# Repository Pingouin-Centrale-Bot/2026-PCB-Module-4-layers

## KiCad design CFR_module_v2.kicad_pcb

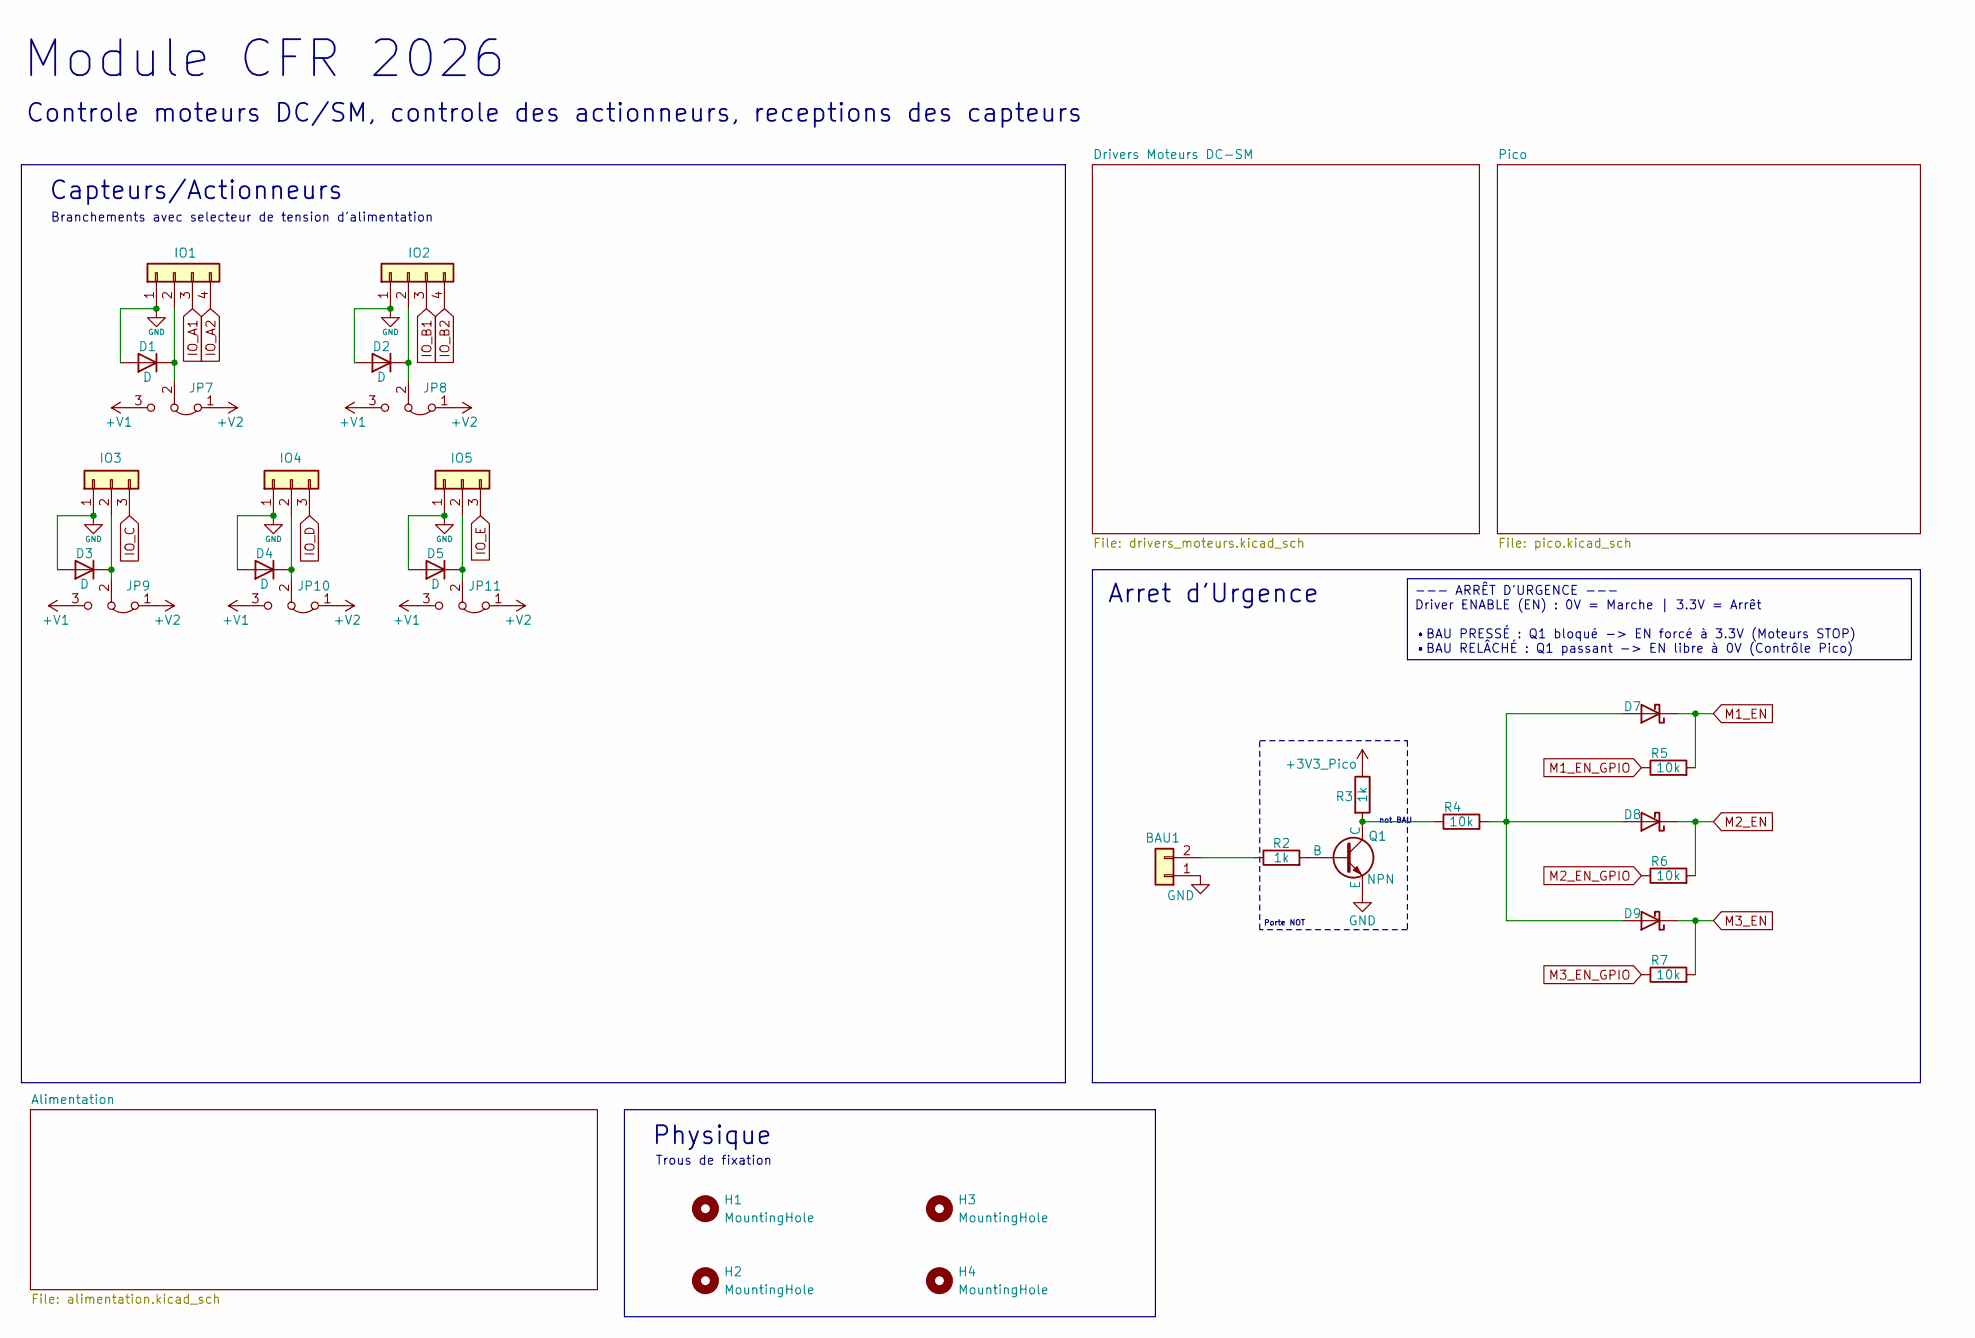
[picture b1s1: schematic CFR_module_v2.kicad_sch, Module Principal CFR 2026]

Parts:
BAU1: Conn_01x02; JST_XH_S2B-XH-A_1x02_P2.50mm_Horizontal
D1, D2, D3, D4, D5: D; D_SMA_Handsoldering
D7, D8, D9: D_Schottky; D_SOD-123
H1, H2, H3, H4: MountingHole; MountingHole_3.2mm_M3
IO1, IO2: Conn_01x04; JST_XH_S4B-XH-A_1x04_P2.50mm_Horizontal
IO3, IO4, IO5: Conn_01x03; JST_XH_S3B-XH-A_1x03_P2.50mm_Horizontal
JP7, JP8, JP9, JP10, JP11: Jumper_3_Bridged12; PinHeader_1x03_P2.54mm_Vertical
Q1: NPN; SOT-23
R2, R3: 1k; R_0805_2012Metric_Pad1.20x1.40mm_HandSolder
R4, R5, R6, R7: 10k; R_0805_2012Metric_Pad1.20x1.40mm_HandSolder

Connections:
+3V3_Pico: R3.1; also elsewhere on the board
+V1: JP7.3 (B), JP8.3 (B), JP9.3 (B), JP10.3 (B), JP11.3 (B); also elsewhere on the board
+V2: JP7.1 (A), JP8.1 (A), JP9.1 (A), JP10.1 (A), JP11.1 (A); also elsewhere on the board
GND: BAU1.1, D1.2 (A), D2.2 (A), D3.2 (A), D4.2 (A), D5.2 (A), IO1.1, IO2.1, IO3.1, IO4.1, IO5.1, Q1.3 (E); also elsewhere on the board
IO_A1: IO1.3; also elsewhere on the board
IO_A2: IO1.4; also elsewhere on the board
IO_B1: IO2.3; also elsewhere on the board
IO_B2: IO2.4; also elsewhere on the board
IO_C: IO3.3; also elsewhere on the board
IO_D: IO4.3; also elsewhere on the board
IO_E: IO5.3; also elsewhere on the board
M1_EN: D7.1 (K), R5.2; also elsewhere on the board
M1_EN_GPIO: R5.1; also elsewhere on the board
M2_EN: D8.1 (K), R6.2; also elsewhere on the board
M2_EN_GPIO: R6.1; also elsewhere on the board
M3_EN: D9.1 (K), R7.2; also elsewhere on the board
M3_EN_GPIO: R7.1; also elsewhere on the board
unnamed: BAU1.2, R2.1
unnamed: D1.1 (K), IO1.2, JP7.2 (C)
unnamed: D2.1 (K), IO2.2, JP8.2 (C)
unnamed: D3.1 (K), IO3.2, JP9.2 (C)
unnamed: D4.1 (K), IO4.2, JP10.2 (C)
unnamed: D5.1 (K), IO5.2, JP11.2 (C)
unnamed: D7.2 (A), D8.2 (A), D9.2 (A), R4.2
unnamed: Q1.2 (B), R2.2
unnamed: Q1.1 (C), R3.2, R4.1

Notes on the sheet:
Physique
Controle moteurs DC/SM, controle des actionneurs, receptions des capteurs
Trous de fixation
Module CFR 2026
Porte NOT
Capteurs/Actionneurs
not BAU
Branchements avec selecteur de tension d'alimentation
Arret d'Urgence
--- ARRÊT D'URGENCE --- Driver ENABLE (EN) : 0V = Marche | 3.3V = Arrêt •BAU PRESSÉ : Q1 bloqué -> EN forcé à 3.3V (Moteurs STOP) •BAU RELÂCHÉ : Q1 passant -> EN libre à 0V (Contrôle Pico)

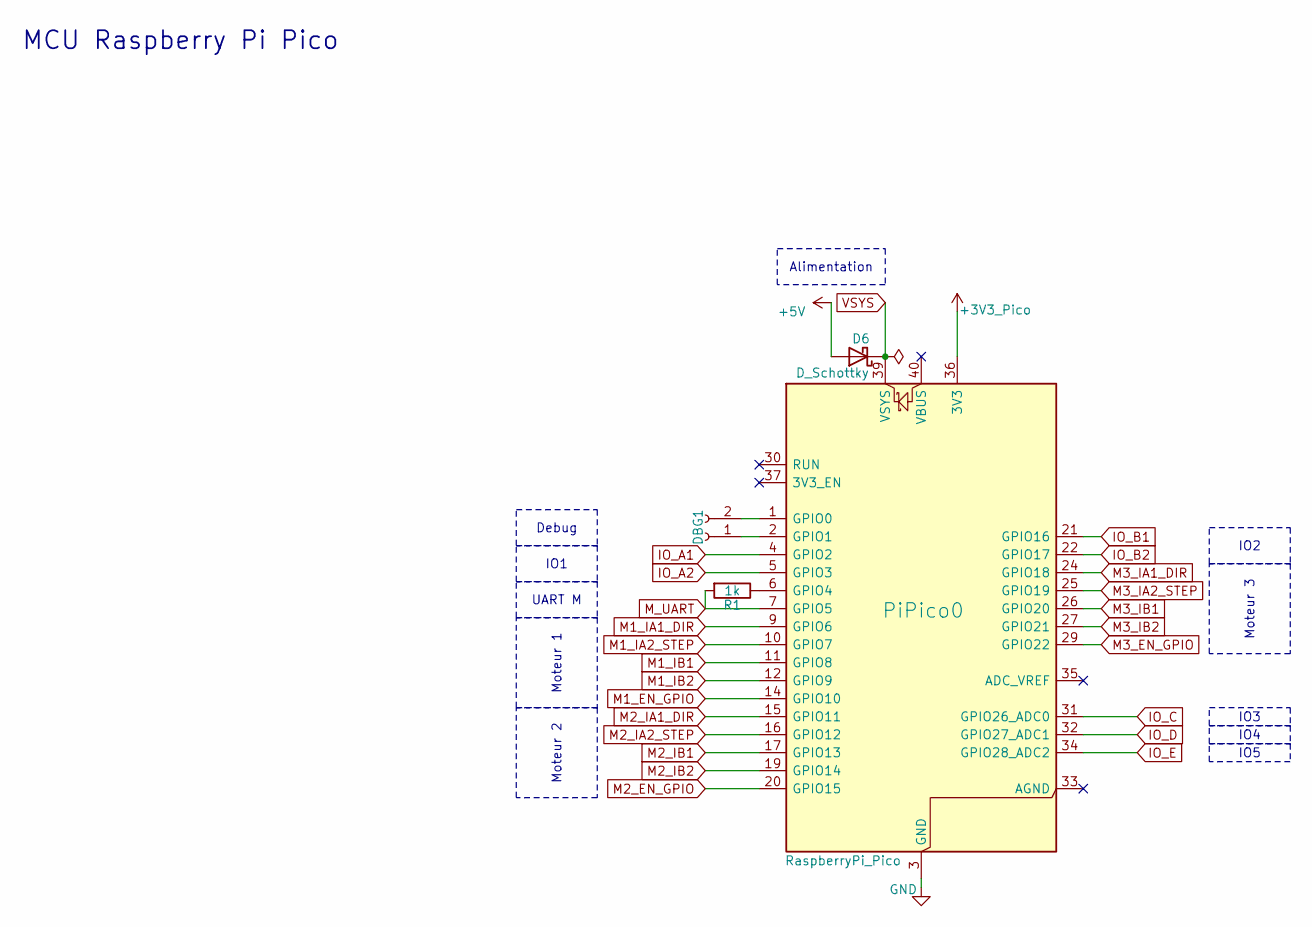
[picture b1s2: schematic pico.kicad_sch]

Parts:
D6: D_Schottky; D_SOD-123
DBG1: Conn_01x02_Socket; JST_XH_S2B-XH-A_1x02_P2.50mm_Horizontal
PiPico0: RaspberryPi_Pico; RaspberryPi_Pico_Common_SMD
R1: 1k; R_0805_2012Metric_Pad1.20x1.40mm_HandSolder

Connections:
+3V3_Pico: PiPico0.36 (3V3); also elsewhere on the board
+5V: D6.2 (A); also elsewhere on the board
GND: PiPico0.3 (GND), PiPico0.8 (GND), PiPico0.13 (GND), PiPico0.18 (GND), PiPico0.23 (GND), PiPico0.28 (GND), PiPico0.38 (GND); also elsewhere on the board
IO_A1: PiPico0.4 (GPIO2); also elsewhere on the board
IO_A2: PiPico0.5 (GPIO3); also elsewhere on the board
IO_B1: PiPico0.21 (GPIO16); also elsewhere on the board
IO_B2: PiPico0.22 (GPIO17); also elsewhere on the board
IO_C: PiPico0.31 (GPIO26_ADC0); also elsewhere on the board
IO_D: PiPico0.32 (GPIO27_ADC1); also elsewhere on the board
IO_E: PiPico0.34 (GPIO28_ADC2); also elsewhere on the board
M1_EN_GPIO: PiPico0.14 (GPIO10); also elsewhere on the board
M1_IA1_DIR: PiPico0.9 (GPIO6); also elsewhere on the board
M1_IA2_STEP: PiPico0.10 (GPIO7); also elsewhere on the board
M1_IB1: PiPico0.11 (GPIO8); also elsewhere on the board
M1_IB2: PiPico0.12 (GPIO9); also elsewhere on the board
M2_EN_GPIO: PiPico0.20 (GPIO15); also elsewhere on the board
M2_IA1_DIR: PiPico0.15 (GPIO11); also elsewhere on the board
M2_IA2_STEP: PiPico0.16 (GPIO12); also elsewhere on the board
M2_IB1: PiPico0.17 (GPIO13); also elsewhere on the board
M2_IB2: PiPico0.19 (GPIO14); also elsewhere on the board
M3_EN_GPIO: PiPico0.29 (GPIO22); also elsewhere on the board
M3_IA1_DIR: PiPico0.24 (GPIO18); also elsewhere on the board
M3_IA2_STEP: PiPico0.25 (GPIO19); also elsewhere on the board
M3_IB1: PiPico0.26 (GPIO20); also elsewhere on the board
M3_IB2: PiPico0.27 (GPIO21); also elsewhere on the board
M_UART: PiPico0.7 (GPIO5), R1.2; also elsewhere on the board
unnamed: DBG1.1, PiPico0.2 (GPIO1)
unnamed: DBG1.2, PiPico0.1 (GPIO0)
unnamed: PiPico0.6 (GPIO4), R1.1
VSYS: D6.1 (K), PiPico0.39 (VSYS)

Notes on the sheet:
MCU Raspberry Pi Pico
IO5
IO4
IO3
Alimentation
Moteur 1
Moteur 2
UART M
IO1
Moteur 3
Debug
IO2

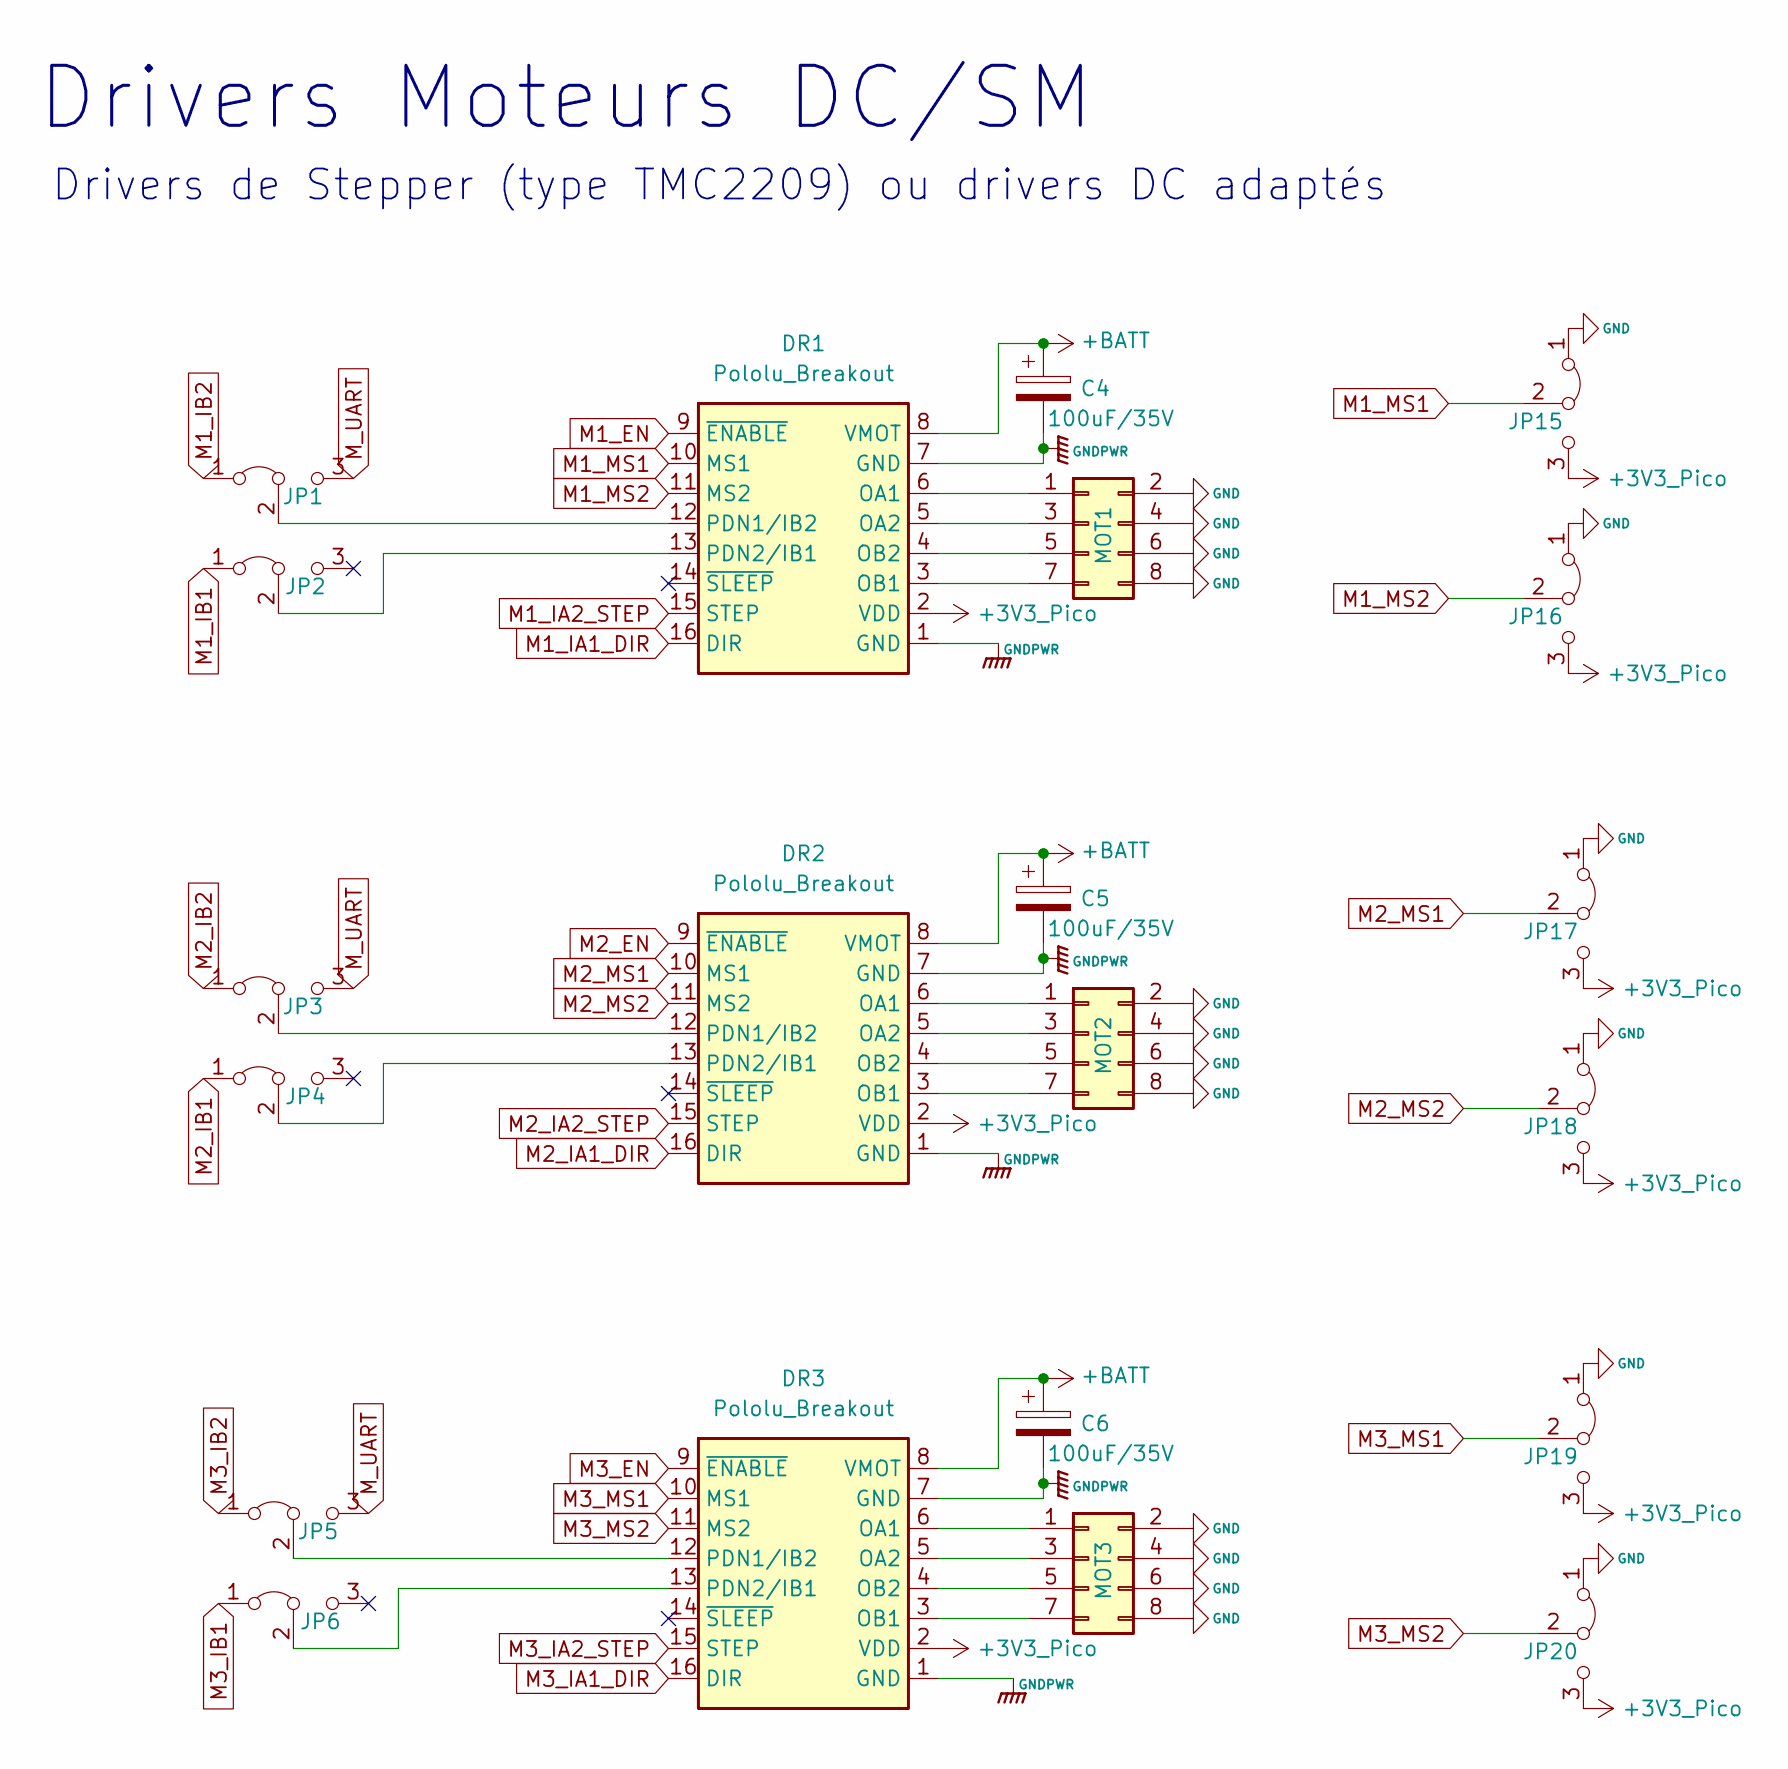
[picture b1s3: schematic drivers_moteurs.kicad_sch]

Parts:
C4, C5, C6: 100uF/35V; CP_Elec_6.3x7.7
DR1, DR2, DR3: Pololu_Breakout; Pololu_Breakout-16_15.2x20.3mm_Better_Silkscreen
JP1, JP2, JP3, JP4, JP5, JP6, JP15, JP16, JP17, JP18, JP19, JP20: Jumper_3_Bridged12; PinHeader_1x03_P2.54mm_Vertical
MOT1, MOT2, MOT3: Conn_02x04_Odd_Even; PinHeader_2x04_P2.54mm_Horizontal

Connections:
+3V3_Pico: DR1.2 (VDD), DR2.2 (VDD), DR3.2 (VDD), JP15.3 (B), JP16.3 (B), JP17.3 (B), JP18.3 (B), JP19.3 (B), JP20.3 (B); also elsewhere on the board
+BATT: C4.1, C5.1, C6.1, DR1.8 (VMOT), DR2.8 (VMOT), DR3.8 (VMOT); also elsewhere on the board
GND: C4.2, C5.2, C6.2, DR1.1 (GND), DR1.7 (GND), DR2.1 (GND), DR2.7 (GND), DR3.1 (GND), DR3.7 (GND), JP15.1 (A), JP16.1 (A), JP17.1 (A), JP18.1 (A), JP19.1 (A), JP20.1 (A), MOT1.2, MOT1.4, MOT1.6, MOT1.8, MOT2.2, MOT2.4, MOT2.6, MOT2.8, MOT3.2, MOT3.4, MOT3.6, MOT3.8; also elsewhere on the board
M1_EN: DR1.9 (~ENABLE); also elsewhere on the board
M1_IA1_DIR: DR1.16 (DIR); also elsewhere on the board
M1_IA2_STEP: DR1.15 (STEP); also elsewhere on the board
M1_IB1: JP2.1 (A); also elsewhere on the board
M1_IB2: JP1.1 (A); also elsewhere on the board
M1_MS1: DR1.10 (MS1), JP15.2 (C)
M1_MS2: DR1.11 (MS2), JP16.2 (C)
M2_EN: DR2.9 (~ENABLE); also elsewhere on the board
M2_IA1_DIR: DR2.16 (DIR); also elsewhere on the board
M2_IA2_STEP: DR2.15 (STEP); also elsewhere on the board
M2_IB1: JP4.1 (A); also elsewhere on the board
M2_IB2: JP3.1 (A); also elsewhere on the board
M2_MS1: DR2.10 (MS1), JP17.2 (C)
M2_MS2: DR2.11 (MS2), JP18.2 (C)
M3_EN: DR3.9 (~ENABLE); also elsewhere on the board
M3_IA1_DIR: DR3.16 (DIR); also elsewhere on the board
M3_IA2_STEP: DR3.15 (STEP); also elsewhere on the board
M3_IB1: JP6.1 (A); also elsewhere on the board
M3_IB2: JP5.1 (A); also elsewhere on the board
M3_MS1: DR3.10 (MS1), JP19.2 (C)
M3_MS2: DR3.11 (MS2), JP20.2 (C)
M_UART: JP1.3 (B), JP3.3 (B), JP5.3 (B); also elsewhere on the board
unnamed: DR1.6 (OA1), MOT1.1
unnamed: DR1.5 (OA2), MOT1.3
unnamed: DR1.3 (OB1), MOT1.7
unnamed: DR1.4 (OB2), MOT1.5
unnamed: DR1.12 (PDN1/IB2), JP1.2 (C)
unnamed: DR1.13 (PDN2/IB1), JP2.2 (C)
unnamed: DR2.6 (OA1), MOT2.1
unnamed: DR2.5 (OA2), MOT2.3
unnamed: DR2.3 (OB1), MOT2.7
unnamed: DR2.4 (OB2), MOT2.5
unnamed: DR2.12 (PDN1/IB2), JP3.2 (C)
unnamed: DR2.13 (PDN2/IB1), JP4.2 (C)
unnamed: DR3.6 (OA1), MOT3.1
unnamed: DR3.5 (OA2), MOT3.3
unnamed: DR3.3 (OB1), MOT3.7
unnamed: DR3.4 (OB2), MOT3.5
unnamed: DR3.12 (PDN1/IB2), JP5.2 (C)
unnamed: DR3.13 (PDN2/IB1), JP6.2 (C)

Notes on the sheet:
Drivers de Stepper (type TMC2209) ou drivers DC adaptés
Drivers Moteurs DC/SM

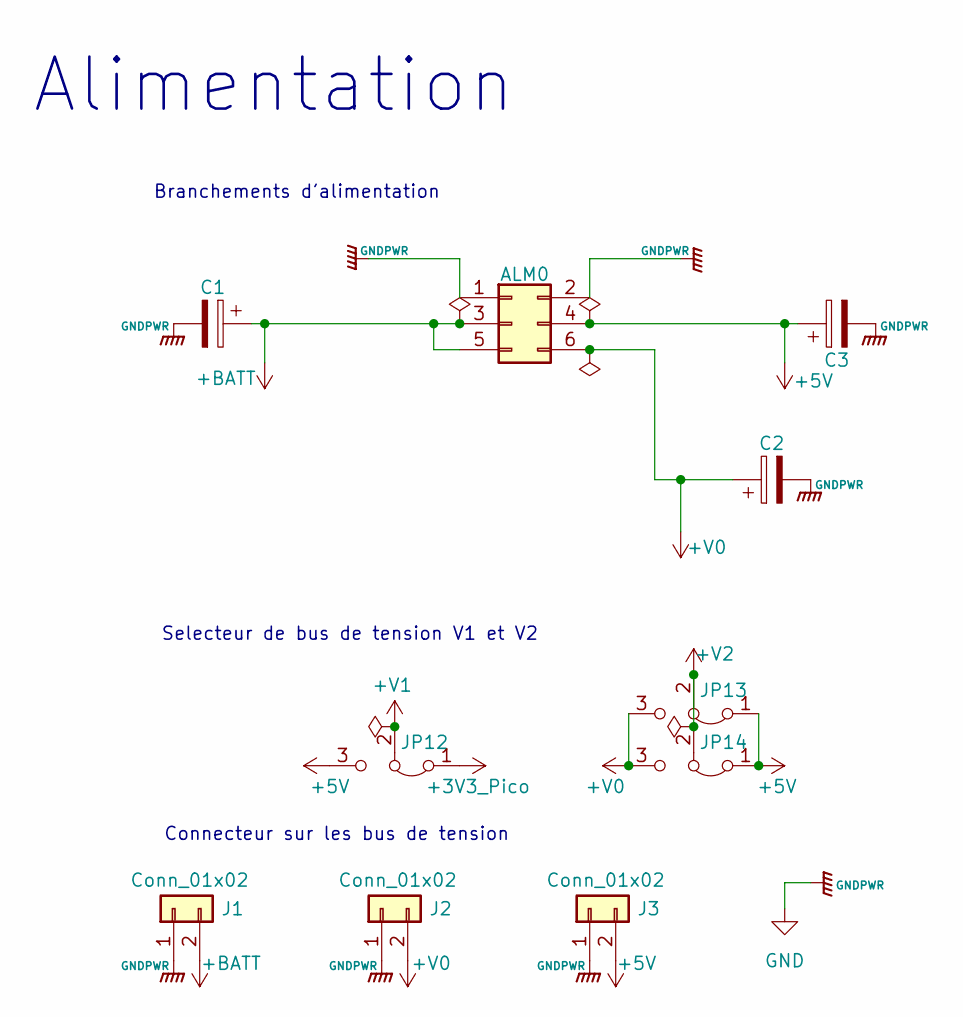
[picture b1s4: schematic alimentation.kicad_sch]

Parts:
ALM0: Conn_02x03_Odd_Even; Molex_Mini-Fit_Jr_5569-06A2_2x03_P4.20mm_Horizontal
C1: C_Polarized; CP_Elec_10x10.5
C2: C_Polarized; CP_Elec_8x10
C3: C_Polarized; CP_Elec_6.3x7.7
J1, J2, J3: Conn_01x02; JST_XH_S2B-XH-A_1x02_P2.50mm_Horizontal
JP12, JP13, JP14: Jumper_3_Bridged12; PinHeader_1x03_P2.54mm_Vertical

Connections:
+3V3_Pico: JP12.1 (A); also elsewhere on the board
+5V: ALM0.4, C3.1, J3.2, JP12.3 (B), JP13.1 (A), JP14.1 (A); also elsewhere on the board
+BATT: ALM0.3, ALM0.5, C1.1, J1.2; also elsewhere on the board
+V0: ALM0.6, C2.1, J2.2, JP13.3 (B), JP14.3 (B)
+V1: JP12.2 (C); also elsewhere on the board
+V2: JP13.2 (C), JP14.2 (C); also elsewhere on the board
GND: ALM0.1, ALM0.2, C1.2, C2.2, C3.2, J1.1, J2.1, J3.1; also elsewhere on the board

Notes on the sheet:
Selecteur de bus de tension V1 et V2
Alimentation
Branchements d'alimentation
Connecteur sur les bus de tension

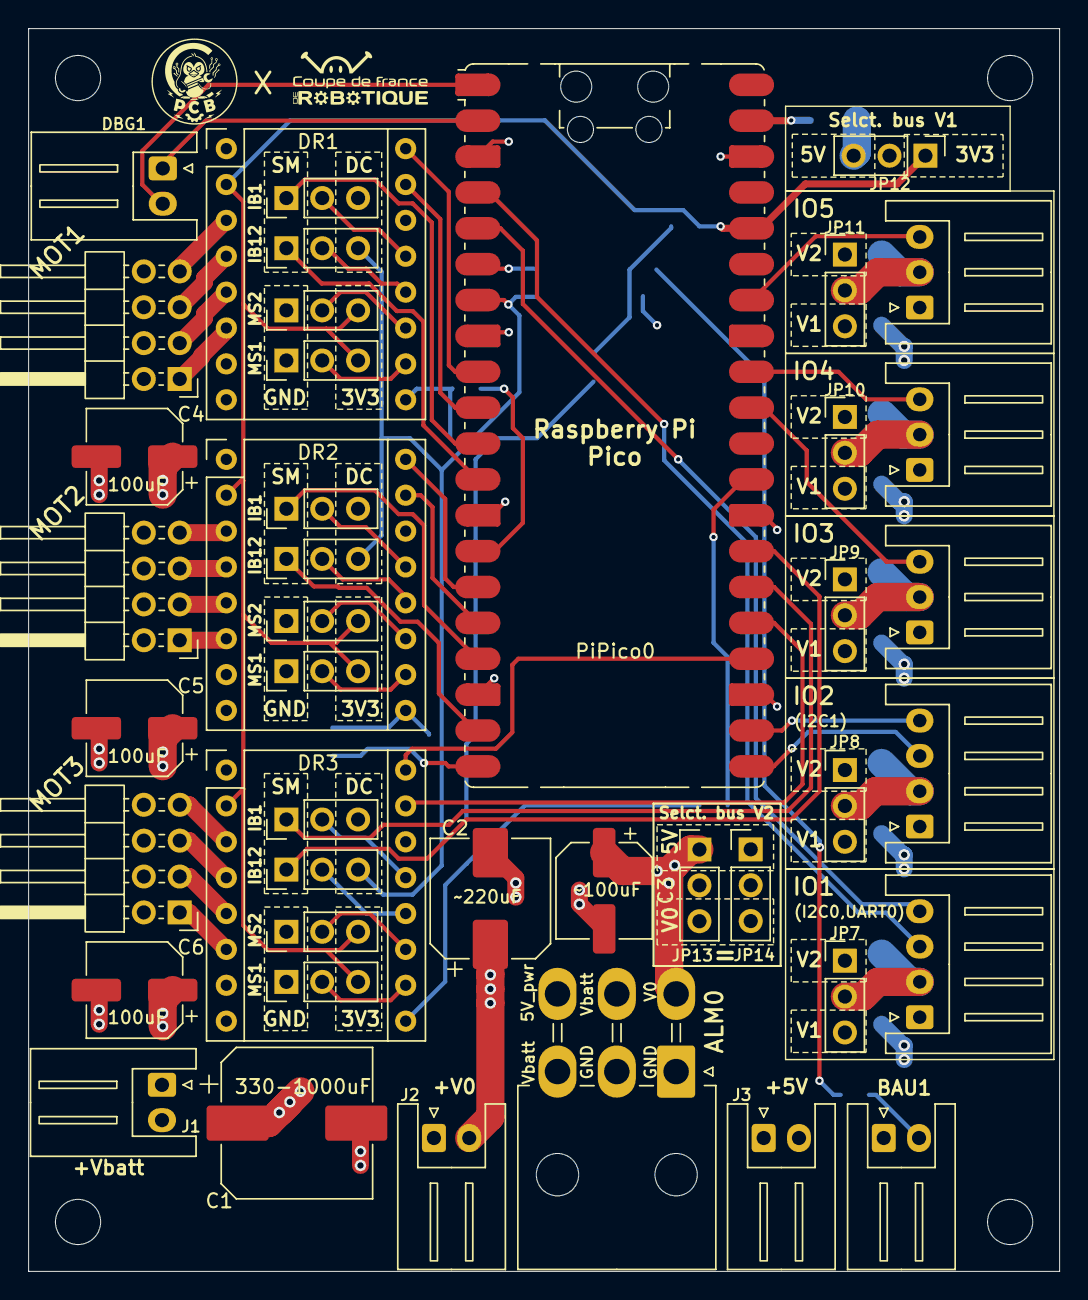
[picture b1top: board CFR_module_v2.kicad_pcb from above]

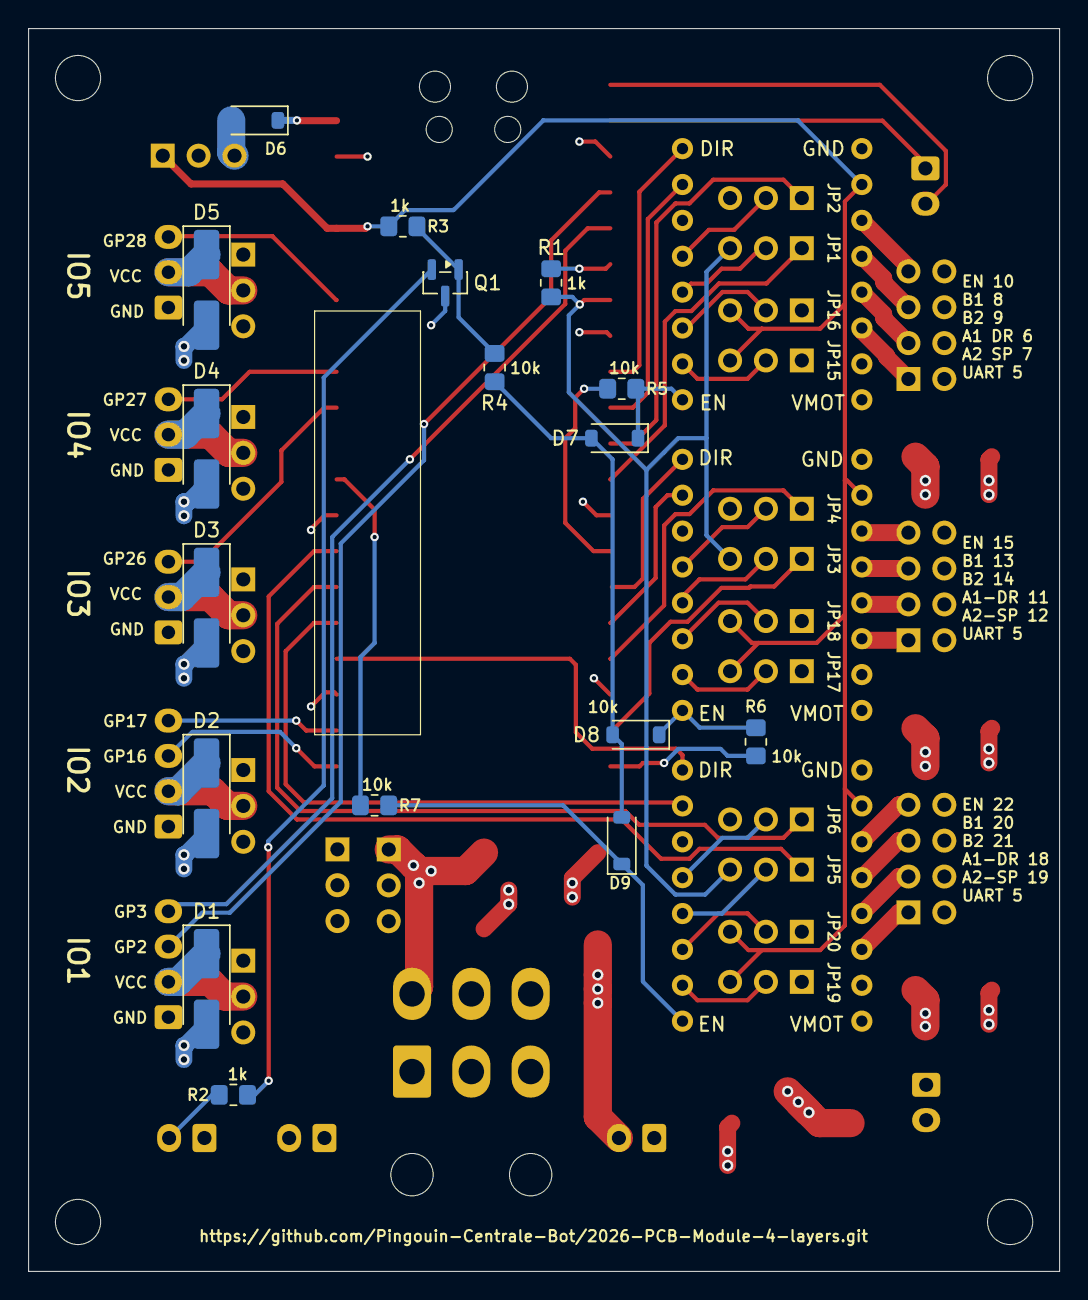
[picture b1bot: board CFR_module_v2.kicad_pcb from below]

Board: 4 copper layers, 73.0 x 88.0 mm, 65 parts (17 on the bottom side), 70 nets.

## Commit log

2026-03-25 placement des empreintes début
2026-03-29 tout connecté
2026-03-29 v2 finalisé
2026-04-03 paufinement
2026-04-03 correction erreurs DRC
